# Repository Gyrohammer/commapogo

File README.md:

# CommaPOGO
I recently have come across a project for the Comma3X that utilizes pogo pins for the quick disconnect of a comma3x. This is my attempt to create an open source alternative to that mount that is DIY and 3D printable. I was inspired after seeing the mount that @cloudj0816 made in the [OpenPilot community discord](https://discord.com/invite/avCJxEX). All credit goes to him for this initial idea! If you'd like to purchase one of his connectors (full CNC metal), you can find the wait list in the #hw-unofficial channel. 

## Goals:
- Inexpensive
- Open Source
- 3D Printed
- ~~Angle adjustment (for imperfect mounting positions)~~
    - This is more of a future goal. I'm first going to focus on getting the static mount correct.

## Progress Tracking
### Parts
Preliminary BOM: 
| Colloqiual Name| Part No.    | Quantity | 
| --------- | -------- | ------- | 
| Pogo Pin  | ~~2906-4-15-20-75-14-11-0~~  | ~~14~~ |
| USB-C Connector | ~~HC005-1A1H1A103-0HR~~ | 2 |
| ASA Filament | n/a | <100g |
| K&J Magnets | D83-N52 | 4 |
|3M Adhesive | 3M™ VHB™ Tape 5952 | ~100mm<sup>2</sup> (~1.5in<sup>2</sup>)|

- [x] Pogo Pins
- [x] USB-C Connector
- [x] Magnets
- [x] Adhesive
#
### Board Development
- [x] General layout
- [x] Trace routing
- [x] Trace power calculations - Data analysis pending (2/15/24)
#### MKI Development
- [x] Initial refinement (MKI)
- [x] Finalization
- [x] Ordered 
- [x] Testing - Failed
- [x] Troubleshooting/diagnosis begins for MKI
- [x] Results finalized, head into next revision.  
#### MKII Development
- [x] Secondary Refinement (MKII)
- [x] Ordered
- [x] Testing - Failed
- [x] Troubleshooting/diagnosis begins for MKII
- [x] Project frozen.
- [ ] Results finalized, head into next (final) revision.
#### MKIII Development
- [ ] Tertiary Refinement (MKIII)
- [ ] Ordered
- [ ] Testing
- [ ] Troubleshooting/diagnosis begins for MKIII
- [ ] Results finalized.

#
### C3X Windshield Mount
- [x] PCB imported and modeled.
- [x] Male mount modeled
- [x] Female mount modeled
- [x] Mock-up mount printed.
- [x] Mount refinement
- [x] Test-bed mounts printed
- [x] Test-beds tested
- [x] 'Gravimatrix' mock-up printed
- [x] Project frozen.
- [ ] 'Gravimatrix' refinement - Minor adjustments being made
- [ ] Preliminary testing
- [ ] Production unit trials
#
### Field Testing
- [ ] Endurance testing (50 hours usage)
- [ ] Vibration testing
- [ ] Heat testing (7 day constant connectivity)
#
## Specifications Pertaining to the Project
- Comma3X Weight: 311g (11oz)
- Power Usage: See the [summary spreadsheet](/power_data/summary.xlsx) for this data.
#
## Separate Updates

### March 10th, 2024
I've gotten the first hand-built boards put together and making a solid connection! The most likely candidate for the mounting system will be the Gravimatrix design, as that is the most solid. But as of 3/10/24 I have a working prototype! Soldering USB-C connectors by hand is extremely difficult, who'da thunk it?

These connectors will likely be soldered on from the manufacturer going forward, this will ensure consistency and quality at the cost of a few cents per board. A compromise I am more than willing to make.

### March 19th, 2024

PCB no worky! I believe I have some crosstalk/interference throughout the coupler. I'll be re-assessing and redesigning the PCB to hopefully counteract this and get a working connection.

### March 21st, 2024

This weekend I'll be using an oscilloscope to check signal integrity. Hopefully its simple as that, and adding a ground plane(s) will solve it. I had no idea what a ground-plane was until I asked for ideas/advice on the electrical engineering stack exchange. [Heres the thread where that was suggested!](https://electronics.stackexchange.com/questions/706633/usb-c-pogo-pin-coupler-troubleshooting).

### April 10th, 2024

Oscilloscope readings showed little to no interference. Messages were coming and going normally, with solid definition. The second PCB design has run into the same error, in the same way. I will be doing some more testing including soldering wires directly from pad-to-pad in an attempt to isolate this to one component. If that doesnt work, I'll be doing one final re-design before putting this project on hold for a while.

### April 18th, 2024
I finally got around to wiring the pads directly to one another for testing! Bad news is that it still doesnt work. I'm unsure, at this point, why this board doesnt work correctly. I feel as if I'm getting some sort of cross-talk between the connections. I'll be tring one more configuration, flipped, to see if that yields any other results. If this doesnt work then I have a backup plan which involves some consumer-hardware and a 3D printed case to house it. I'm hoping this custom solution works, as I put a lot of time into it, but if not then it is what it is. I should've gotten an EE degree, physics is useless here! Actually it was useful for the magnet force calculations.

### April 22nd, 2024
Unfortunately it seems that I've hit the limit of my knowledge/ability with this project. I cannot get the communication to work correctly across the interlink. I have already spend about $400 in material on this project, putting together another PCB for order would only add to that and would likely not work. Not to mention the hours spent testing and designing the mounts/PCB revisions. This was still an excellent journey to go on! Maybe one day I'll revisit it. This repo does contain some useful info, though, such as power statistics and the weight of the unit, hopefully that will be useful to someone should they stumble across this.

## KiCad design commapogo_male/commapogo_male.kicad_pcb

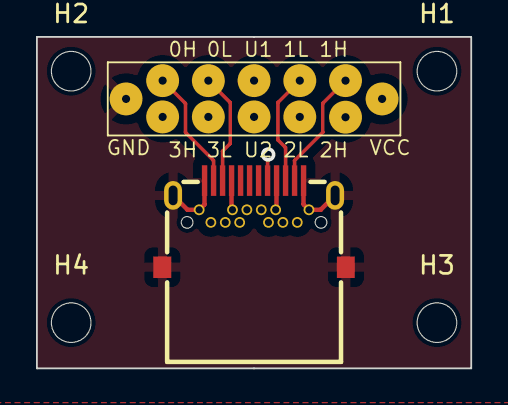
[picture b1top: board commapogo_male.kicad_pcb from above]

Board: 4 copper layers, 24.1 x 18.4 mm, 6 parts (0 on the bottom side), 12 nets.

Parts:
H1, H2, H3, H4: MountingHole; MountingHole_2.2mm_M2
J1: Conn_02x07_Row_Letter_Last; 2x7_Pogo_Male
J2: Conn_02x12_Row_Letter_Last; GT-USB-7001C

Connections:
+12V: J1.14 (Pin_7b), J2.A4 (Pin_4a), J2.A9, J2.B4 (Pin_4b), J2.B9 (Pin_9b)
/CAN0_N: J1.3 (Pin_3a), J2.A3 (Pin_3a)
/CAN0_P: J1.2 (Pin_2a), J2.A2 (Pin_2a)
/CAN1_N: J1.5 (Pin_5a), J2.A10 (Pin_10a)
/CAN1_P: J1.6 (Pin_6a), J2.A11 (Pin_11a)
/CAN2_N: J1.12 (Pin_5b), J2.B3 (Pin_3b)
/CAN2_P: J1.13 (Pin_6b), J2.B2 (Pin_2b)
/CAN3_N: J1.10 (Pin_3b), J2.B10 (Pin_10b)
/CAN3_P: J1.9 (Pin_2b), J2.B11 (Pin_11b)
/SBU1: J1.4 (Pin_4a), J2.A8 (Pin_8a)
/SBU2: J1.11 (Pin_4b), J2.B8 (Pin_8b)
GND: J1.1 (Pin_1a), J2.0, J2.A1 (Pin_1a), J2.A12 (Pin_12a), J2.B1, J2.B12 (Pin_12b)

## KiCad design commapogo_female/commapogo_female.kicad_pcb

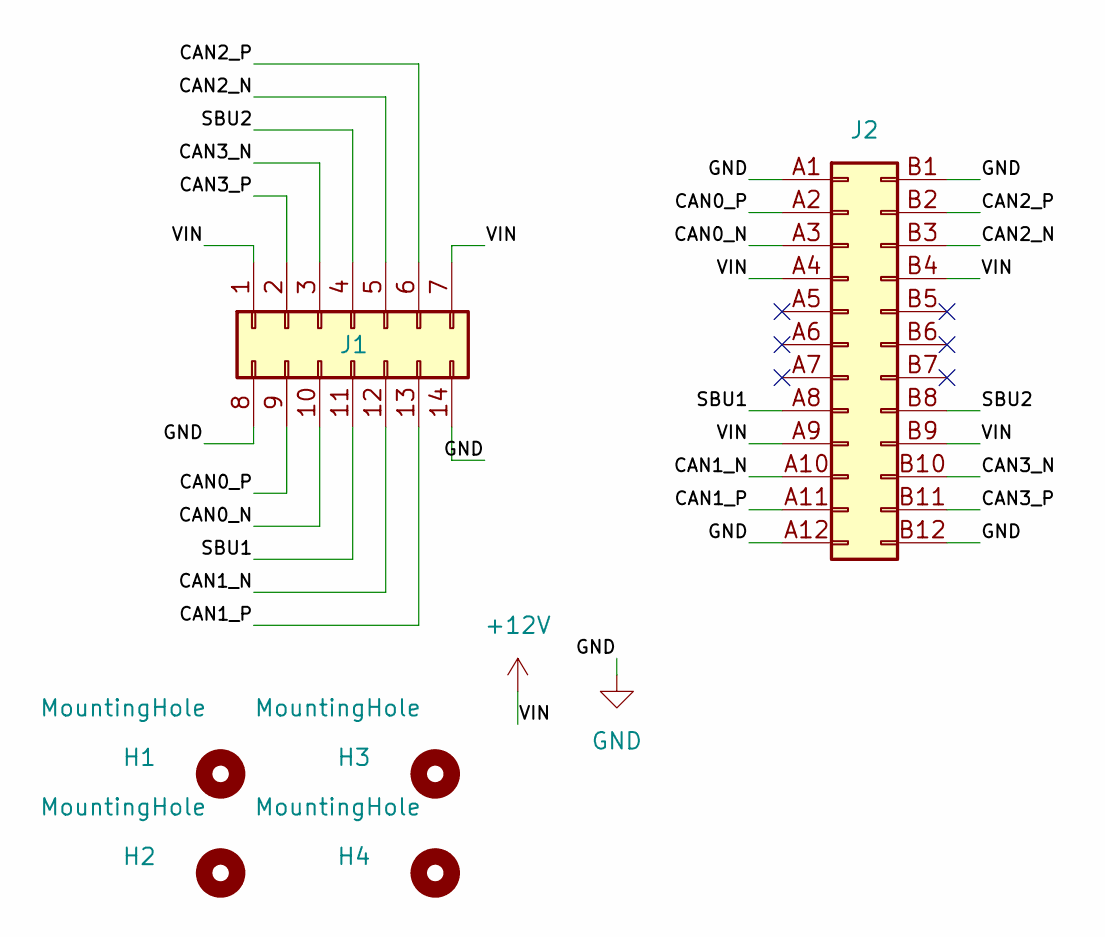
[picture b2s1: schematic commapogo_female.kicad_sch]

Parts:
H1, H2, H3, H4: MountingHole; MountingHole_3mm
J1: Conn_02x07_Row_Letter_Last; 2x7_Pogo_Male
J2: Conn_02x12_Row_Letter_Last; USB-C-SMD_HC005-1A1H1A103-0HR; LCSC C2894904

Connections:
+12V: J1.1 (Pin_1a), J1.7 (Pin_7a), J2.A4 (Pin_4a), J2.A9, J2.B4 (Pin_4b), J2.B9 (Pin_9b)
/CAN0_N: J1.10 (Pin_3b), J2.A3 (Pin_3a)
/CAN0_P: J1.9 (Pin_2b), J2.A2 (Pin_2a)
/CAN1_N: J1.12 (Pin_5b), J2.A10 (Pin_10a)
/CAN1_P: J1.13 (Pin_6b), J2.A11 (Pin_11a)
/CAN2_N: J1.5 (Pin_5a), J2.B3 (Pin_3b)
/CAN2_P: J1.6 (Pin_6a), J2.B2 (Pin_2b)
/CAN3_N: J1.3 (Pin_3a), J2.B10 (Pin_10b)
/CAN3_P: J1.2 (Pin_2a), J2.B11 (Pin_11b)
/SBU1: J1.11 (Pin_4b), J2.A8 (Pin_8a)
/SBU2: J1.4 (Pin_4a), J2.B8 (Pin_8b)
GND: J1.8 (Pin_1b), J1.14 (Pin_7b), J2.1, J2.2, J2.3, J2.4, J2.A1 (Pin_1a), J2.A12 (Pin_12a), J2.B1, J2.B12 (Pin_12b)

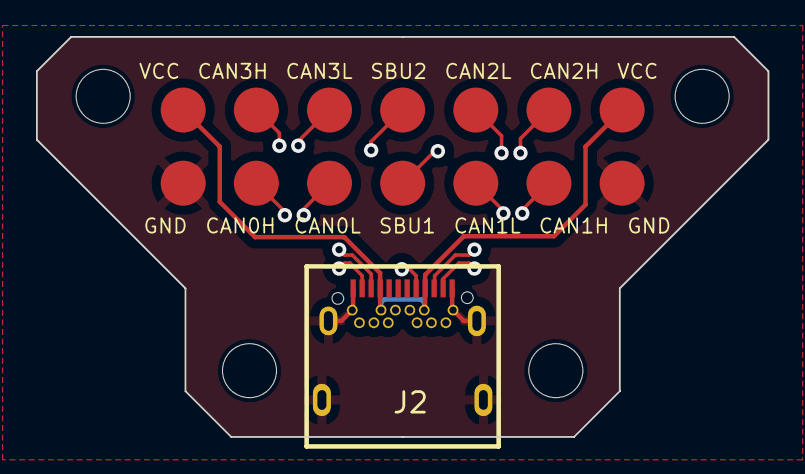
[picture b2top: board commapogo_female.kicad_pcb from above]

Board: 4 copper layers, 40.6 x 22.2 mm, 6 parts (0 on the bottom side), 12 nets.

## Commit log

2024-02-06 add pcb files for initial commit
2024-02-06 add schema file for pcb`
2024-02-06 add visual reference and update pcb schema
2024-02-06 push before eod
2024-02-06 finish wiring schematic for pogo
2024-02-07 refine footprint and schema
2024-02-07 add excel parts tracking list
2024-02-07 refine pcb add mount holes create model
2024-02-07 mock up connector in f360
2024-02-08 organize files into parts
2024-02-08 update parts list with alternatives
2024-02-08 add discord invite, purchase info, fix mention
2024-02-09 add more formats of mount files
2024-02-09 flipped connector again, still incorrect fix later
2024-02-12 fusion360 possible, additional files added
2024-02-12 fixed female connector mirror
2024-02-12 implement silkscreen for debug
2024-02-13 add power data from first run
2024-02-13 fix csv formatting
2024-02-13 fix csv formatting AGAIN
2024-02-13 add c3x power draw and weight
2024-02-13 start c3x mount
2024-02-13 add magnets to bom
2024-02-13 Add dimensions to magnet
2024-02-13 update printable files and parts list
2024-02-14 organize file systems, redo pcb
2024-02-14 add baseline files finalize pcb
2024-02-14 export v1 of unit side mount
2024-02-14 add in prototype directory
2024-02-14 introduce prototype: gravimatrix
2024-02-14 add force calculations add prototype parts
2024-02-14 test excel xml viewing experience
2024-02-14 remove parts list test
2024-02-14 add another magnet to force calc
2024-02-15 upload more power data
2024-02-15 update force calculations
2024-02-15 format power data, more analysis
2024-02-15 update progress and finalization steps
2024-02-15 adjust mount design goals
2024-02-15 continue data analysis, add summary sheet
2024-02-15 add link to power data summary
2024-02-15 pcb finalized, very exciting
2024-02-15 change pogo pin part number
2024-02-15 begin gerber file creation add pogo alternatives
    Pogo pin alternatives were selected for more robust connections. All
    alternatives will be considered with the most likely candidate pushed to
    the readme.
    Gerber file generation has been started, initial files have been made.
    Other parameters will be determined later.
2024-02-15 calculations continued
    Safety factor calculations revised and updated.
2024-02-15 finalize power analysis
2024-02-15 convert xlsx to csv
2024-02-16 multi magnet versions exported to printable files
    four magnet sizes have been chosen for testing purposes. Their models
    and corresponding mounts have been categorized for printing and testing.
2024-02-16 generate gerber files for production
    Orders have been submitted to manufacturer for evaluation.
2024-02-16 update readme with current goals and progress
2024-02-16 update goals change component descriptions
2024-02-16 re-arrange files and folders, update components
2024-02-16 correct description of cloudj connector
2024-02-19 reworked models added testing jig
    All test-bed modules have been reworked to be more 'printer friendly'.
    Print 90deg on the flat side of the unit_side connector for easier
    printing. Still a difficult print, but a tad less so.
    Testing jig has been added for magnet strength. This will be heavily
    revised this is only for light initial shock testing.
2024-02-19 update parts list with bom and other pricing
2024-02-19 increased female smd pad size for slop
2024-02-19 update testing and force calculations
2024-02-20 added quick final files before home
2024-02-21 add new prototype, edit misc excel
2024-02-21 modified polaron prototype unit mount
2024-02-22 update polaron mount
    polaron mount continues to recieve updates, next steps will be testing
    with the actual pcb when it gets to the US
2024-02-22 update road map for current progress
2024-02-22 additional polaron revision
2024-02-22 update BOM with chosen magnets
2024-02-22 corrected magnet type in parts list
2024-02-23 add windshield models and other misc models
2024-02-23 add reworked polaron unit mount stl
2024-02-23 revise force calculations
2024-02-27 update readme add tape spec sheet
2024-03-05 rev2 of boards plus compliant bom
    The female connector has been updated with larger pads for better slop
    compensation.
    A BOM matching the PCBWay format has been implemented for each part to
    aid in manufacturing/assembly.
2024-03-06 update kicad backup and picknplace pos files
2024-03-06 change usb c connector export to jlcpcb
2024-03-06 add gitignore kicad
2024-03-06 adjust file trees and clean up
2024-03-07 update usb c connector and status of project
2024-03-08 change file naming move to archive
2024-03-10 rework usb-c footprint for jlcpcb
2024-03-10 remove female connector backup
2024-03-11 update readme with misc progress
2024-03-11 fix spelling, add proper dates
2024-03-11 add more 3d models to correct directory
    This includes multiple pogo pin guides with differing tolerance values,
    .25, .125, and .07 (flush)
    Gravimatrix prototype has also been updated with some minor changes
2024-03-11 Update/clarify roadmap
2024-03-11 clarify roadmap goals
2024-03-11 remove csv and excel files from gitignore
2024-03-11 upload alternative pogo pin datasheet
2024-03-12 refine gravimatrix
2024-03-12 gravimatrix revision 2
2024-03-12 add additional pogo jigs
2024-03-12 sync male and female backup files
2024-03-13 sort pogo pin jigs into subdirectory
2024-03-14 restructured jig files
2024-03-14 add more pogo jigs to relevant folder
2024-03-14 add component files to folder
2024-03-15 add shorter variant for x-2-x pins
2024-03-15 attach legs to unit side of mount
2024-03-15 add new component sheest for pogo options
2024-03-15 add another pogo data sheet
2024-03-15 cleanup
2024-03-15 cleanup of pogo jig directories
2024-03-18 continue mount revision
2024-03-20 revised PCB
2024-03-20 update readme progress
2024-03-20 new mount design, spec sheets soon
2024-03-21 rework pcb design
2024-03-21 redo pcb design add more ground planes
2024-03-21 upload testing jig for troubleshooting
2024-03-21 upload test jig rework
2024-03-21 update timeline
2024-03-22 revise pcb with proper calculations
2024-03-22 end of cleanup/assortment
2024-03-26 visualize pcb into pdf layout
2024-03-27 added parts list and breakdowns of parts
2024-03-27 update pcb design and sync
2024-03-28 update excel cost tracking sheet
2024-04-05 revise gravimatrix and test jig files
2024-04-05 update new component datasheets and models
2024-04-05 begin creating footprint for final test
2024-04-05 update 700c schematic further
2024-04-05 bring pcb libraries up to date
2024-04-10 revamp pcb design
2024-04-10 update readme with scope results
2024-04-12 update prelim bom to reflect current indecision
    I am unsure as to what pins will work. Further testing is required and will be performed within the next few days.
2024-04-12 Reformat and revise progress for board development.
2024-04-18 Update readme with recent development :-(
2024-04-22 Final push before archive, RIP commaPOGO
